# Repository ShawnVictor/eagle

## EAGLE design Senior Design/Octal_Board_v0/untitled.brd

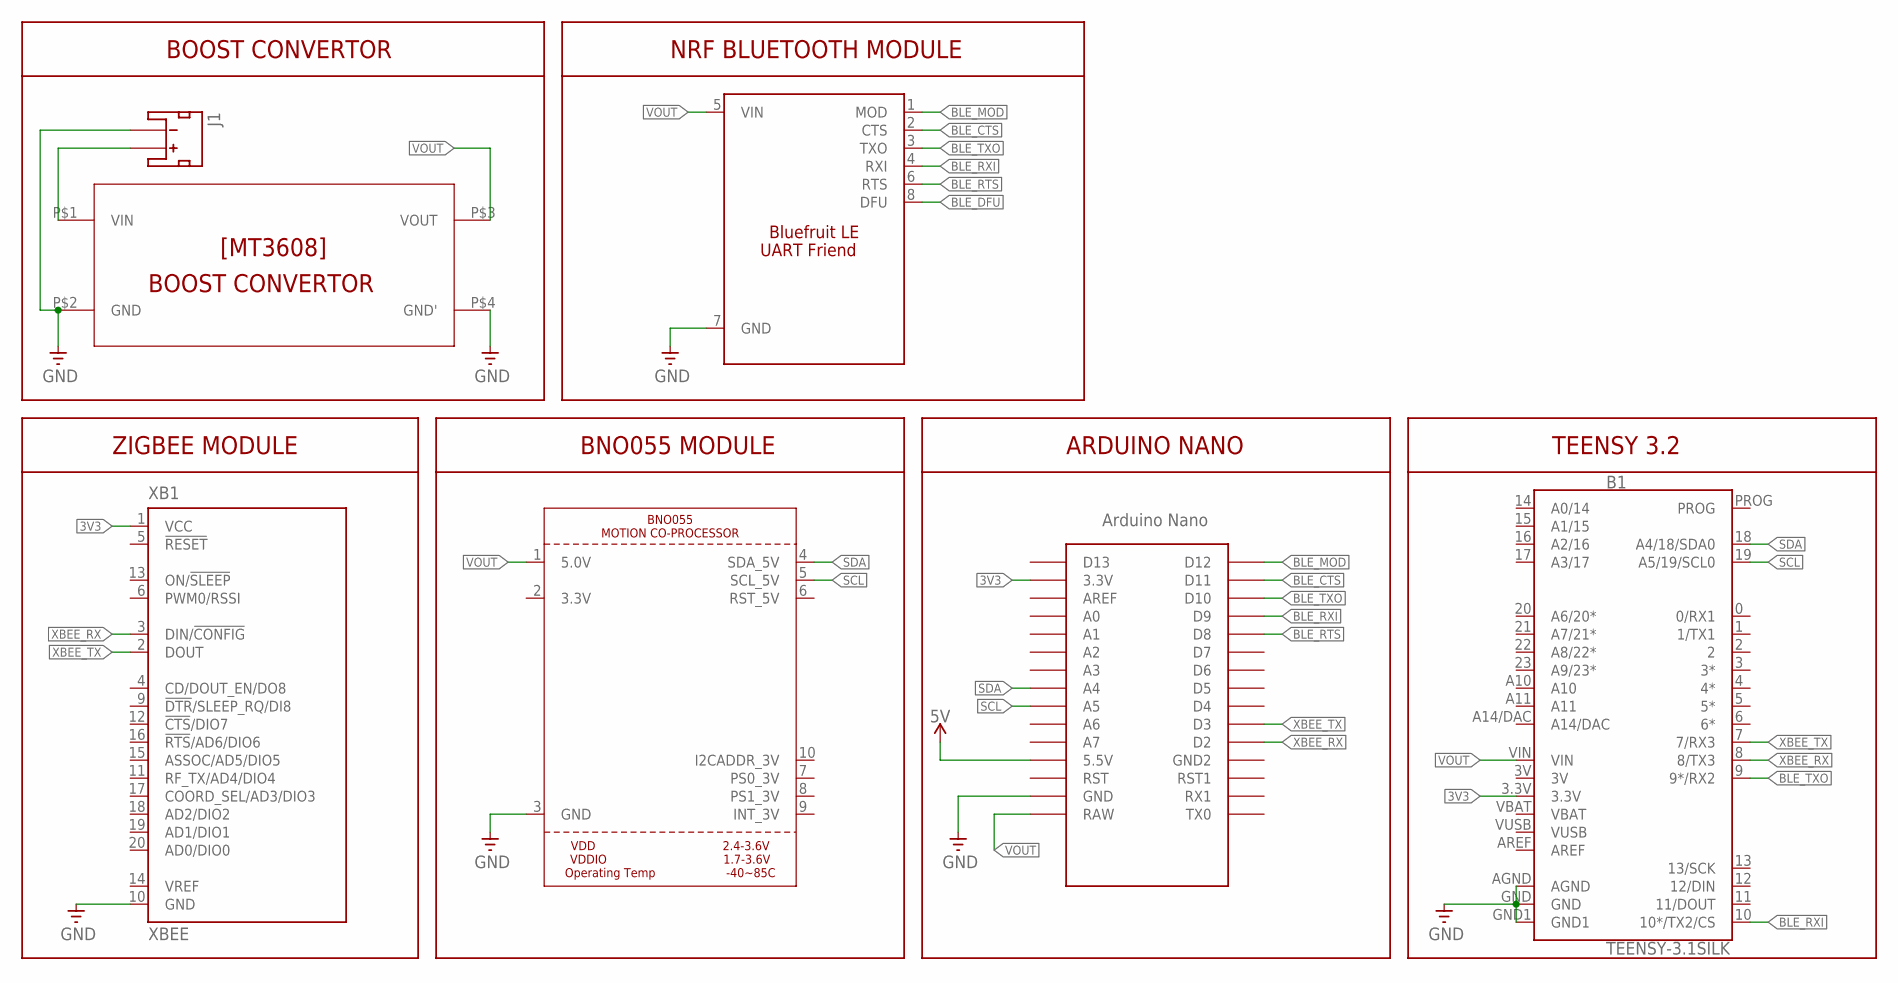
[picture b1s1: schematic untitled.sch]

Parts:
B1: TEENSY-3.1SILK; TEENSY-3.1
J1: JST_2MM_MALE; JST-2-SMD
U$1: NANO
U$2: BNO055; BNO
U$3: MT3608
U$4: BLUEFRUIT_LE; BLUETOOTH_FRIEND
XB1: XBEE

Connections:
3V: B1.3V
3V3: B1.3.3V, U$1.3.3V, XB1.1 (VCC)
5V: U$1.5V (5.5V)
BLE_CTS: U$1.D11, U$4.2 (CTS)
BLE_DFU: U$4.8 (DFU)
BLE_MOD: U$1.D12, U$4.1 (MOD)
BLE_RTS: U$1.D8, U$4.6 (RTS)
BLE_RXI: B1.10 (10*/TX2/CS), U$1.D9, U$4.4 (RXI)
BLE_TXO: B1.9 (9*/RX2), U$1.D10, U$4.3 (TXO)
GND: B1.AGND, B1.GND, B1.GND1, J1.1 (-), U$1.GND, U$2.3 (GND), U$3.P$2 (GND), U$3.P$4 (GND'), U$4.7 (GND), XB1.10 (GND)
unnamed: J1.2 (+), U$3.P$1 (VIN)
SCL: B1.19 (A5/19/SCL0), U$1.A5, U$2.5 (SCL_5V)
SDA: B1.18 (A4/18/SDA0), U$1.A4, U$2.4 (SDA_5V)
VBAT: B1.VBAT
VOUT: B1.VIN, U$1.RAW, U$2.1 (5.0V), U$3.P$3 (VOUT), U$4.5 (VIN)
VUSB: B1.VUSB
XBEE_RX: B1.8 (8/TX3), U$1.D2, XB1.3 (DIN/!CONFIG)
XBEE_TX: B1.7 (7/RX3), U$1.D3, XB1.2 (DOUT)

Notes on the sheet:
ZIGBEE MODULE
BNO055 MODULE
ARDUINO NANO
TEENSY 3.2
BOOST CONVERTOR
NRF BLUETOOTH MODULE

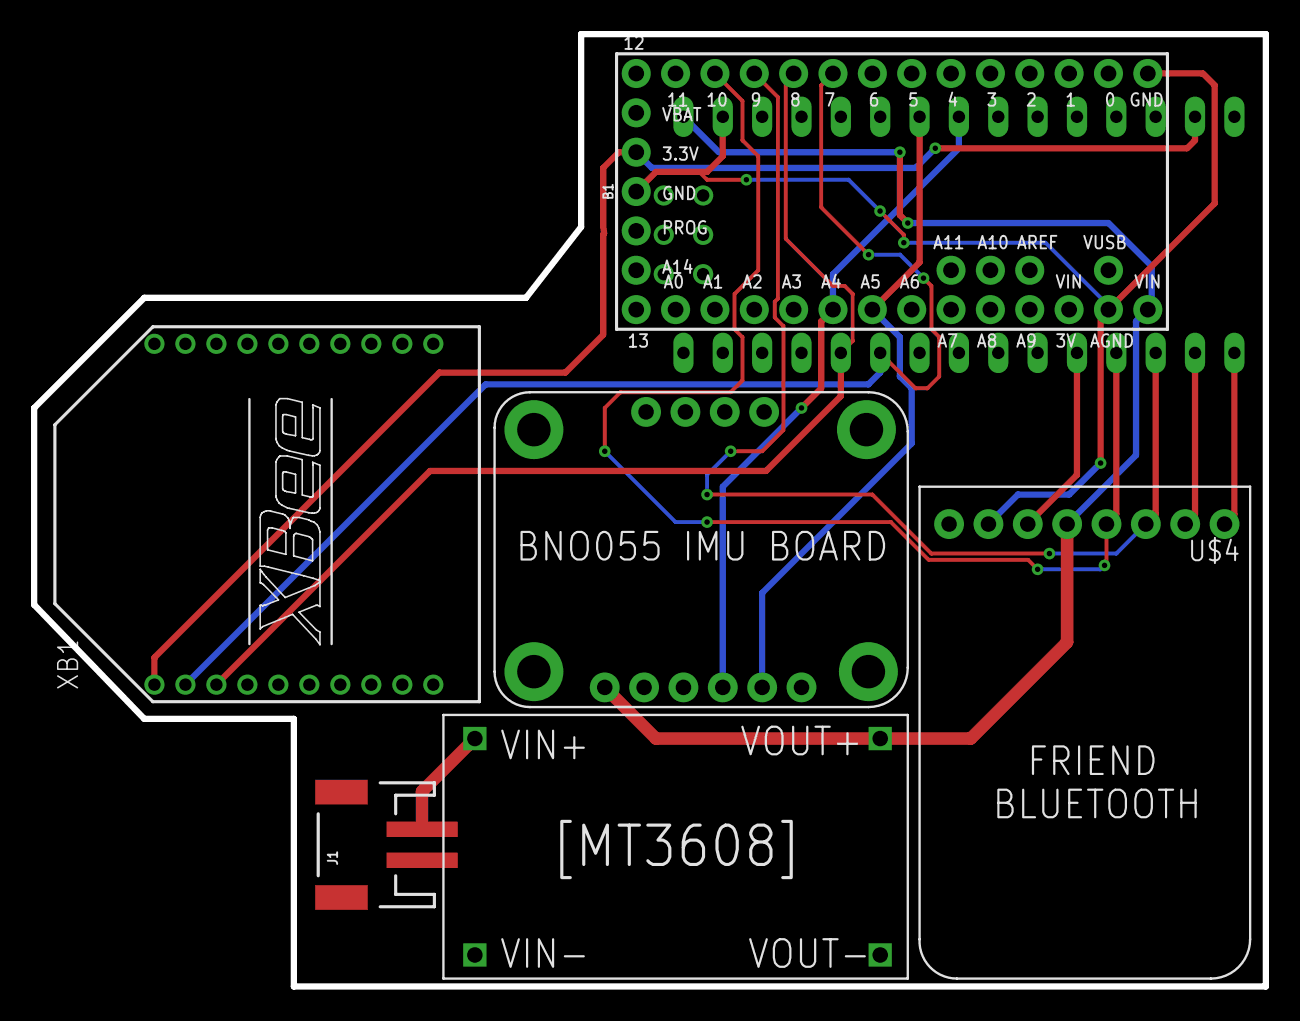
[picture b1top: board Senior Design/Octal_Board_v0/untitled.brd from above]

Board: 2 copper layers, 79.5 x 61.5 mm, 7 parts (0 on the bottom side), 13 nets.

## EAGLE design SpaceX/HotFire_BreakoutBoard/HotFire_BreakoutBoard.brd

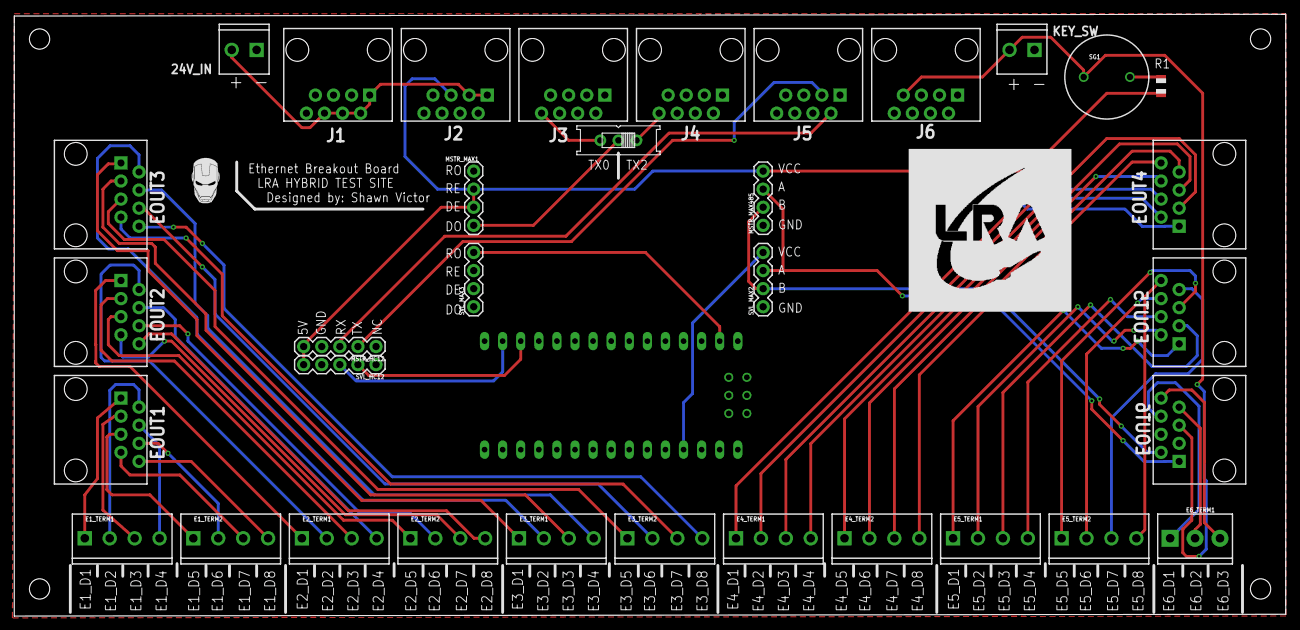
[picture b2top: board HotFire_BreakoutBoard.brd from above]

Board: 2 copper layers, 178.5 x 84.5 mm, 35 parts (0 on the bottom side), 59 nets.

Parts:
24V_IN: SCREWTERMINAL-3.5MM-2
E1_TERM1, E1_TERM2, E2_TERM1, E2_TERM2, E3_TERM1, E3_TERM2, E4_TERM1, E4_TERM2, E5_TERM1, E5_TERM2: SCREWTERMINAL-3.5MM-4
E6_TERM1: SCREWTERMINAL-3.5MM-3
EOUT1, EOUT2, EOUT3, EOUT4, EOUT5, EOUT6: RJ45; RJ45-8
J1, J2, J3, J4, J5, J6: RJ45; RJ45-8
KEY_SW: SCREWTERMINAL-3.5MM-2
MSTR_HC12: 1X05
MSTR_MAX1, MSTR_MAX485: 1X04
R1: 100; R0805
S1: EG1218
SG1: BUZZERPTH; BUZZER-12MM
SVL_HC12: 1X05
SVL_MAX2, SVL_MAX3: 1X04
U$4: NANO

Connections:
5.0V: J2.5, MSTR_HC12.5, MSTR_MAX1.2, MSTR_MAX1.3, MSTR_MAX485.4, R1.2, SVL_HC12.5
+24V: 24V_IN.2, J1.1, J1.2, J1.4, J1.6, J2.1, J2.3
D1/TX0: J3.8, S1.S
D10: SVL_HC12.2, U$4.D10
D11: SVL_HC12.3, U$4.D11
E1_D1: E1_TERM1.1, EOUT1.1
E1_D2: E1_TERM1.2, EOUT1.2
E1_D3: E1_TERM1.3, EOUT1.3
E1_D4: E1_TERM1.4, EOUT1.4
E1_D5: E1_TERM2.1, EOUT1.5
E1_D6: E1_TERM2.2, EOUT1.6
E1_D7: E1_TERM2.3, EOUT1.7
E1_D8: E1_TERM2.4, EOUT1.8
E2_D1: E2_TERM1.1, EOUT2.1
E2_D2: E2_TERM1.2, EOUT2.2
E2_D3: E2_TERM1.3, EOUT2.3
E2_D4: E2_TERM1.4, EOUT2.4
E2_D5: E2_TERM2.1, EOUT2.5
E2_D6: E2_TERM2.2, EOUT2.6
E2_D7: E2_TERM2.3, EOUT2.7
E2_D8: E2_TERM2.4, EOUT2.8
E3_D1: E3_TERM1.1, EOUT3.1
E3_D2: E3_TERM1.2, EOUT3.2
E3_D3: E3_TERM1.3, EOUT3.3
E3_D4: E3_TERM1.4, EOUT3.4
E3_D5: E3_TERM2.1, EOUT3.5
E3_D6: E3_TERM2.2, EOUT3.6
E3_D7: E3_TERM2.3, EOUT3.7
E3_D8: E3_TERM2.4, EOUT3.8
E4_D1: E4_TERM1.1, EOUT4.1
E4_D2: E4_TERM1.2, EOUT4.2
E4_D3: E4_TERM1.3, EOUT4.3
E4_D4: E4_TERM1.4, EOUT4.4
E4_D5: E4_TERM2.1, EOUT4.5
E4_D6: E4_TERM2.2, EOUT4.6
E4_D7: E4_TERM2.3, EOUT4.7
E4_D8: E4_TERM2.4, EOUT4.8
E5_D1: E5_TERM1.1, EOUT5.1
E5_D2: E5_TERM1.2, EOUT5.2
E5_D3: E5_TERM1.3, EOUT5.3
E5_D4: E5_TERM1.4, EOUT5.4
E5_D5: E5_TERM2.1, EOUT5.5
E5_D6: E5_TERM2.2, EOUT5.6
E5_D7: E5_TERM2.3, EOUT5.7
E5_D8: E5_TERM2.4, EOUT5.8
E6_D1: E6_TERM1.1, EOUT6.6
E6_D2: E6_TERM1.2, EOUT6.7
E6_D3: E6_TERM1.3, EOUT6.8
ETHERNET8: J4.8, S1.O
ETHERNET10: J5.2, MSTR_HC12.3
ETHERNET11: J5.3, MSTR_HC12.2
GND: 24V_IN.1, EOUT6.3, EOUT6.4, J1.8, J6.8, KEY_SW.1, MSTR_HC12.4, MSTR_MAX485.1, SVL_HC12.4, SVL_MAX2.1, SVL_MAX3.2, SVL_MAX3.3, U$4.GND
KEY_SW+: EOUT6.5, J6.7, KEY_SW.2, SG1.-
MAX_A: EOUT6.1, MSTR_MAX485.3, SVL_MAX2.3
MAX_B: EOUT6.2, MSTR_MAX485.2, SVL_MAX2.2
unnamed: MSTR_MAX1.1, S1.P
unnamed: R1.1, SG1.+
SLV_RX: SVL_MAX3.4, U$4.RX1
SVL_5V: SVL_MAX2.4, U$4.5V

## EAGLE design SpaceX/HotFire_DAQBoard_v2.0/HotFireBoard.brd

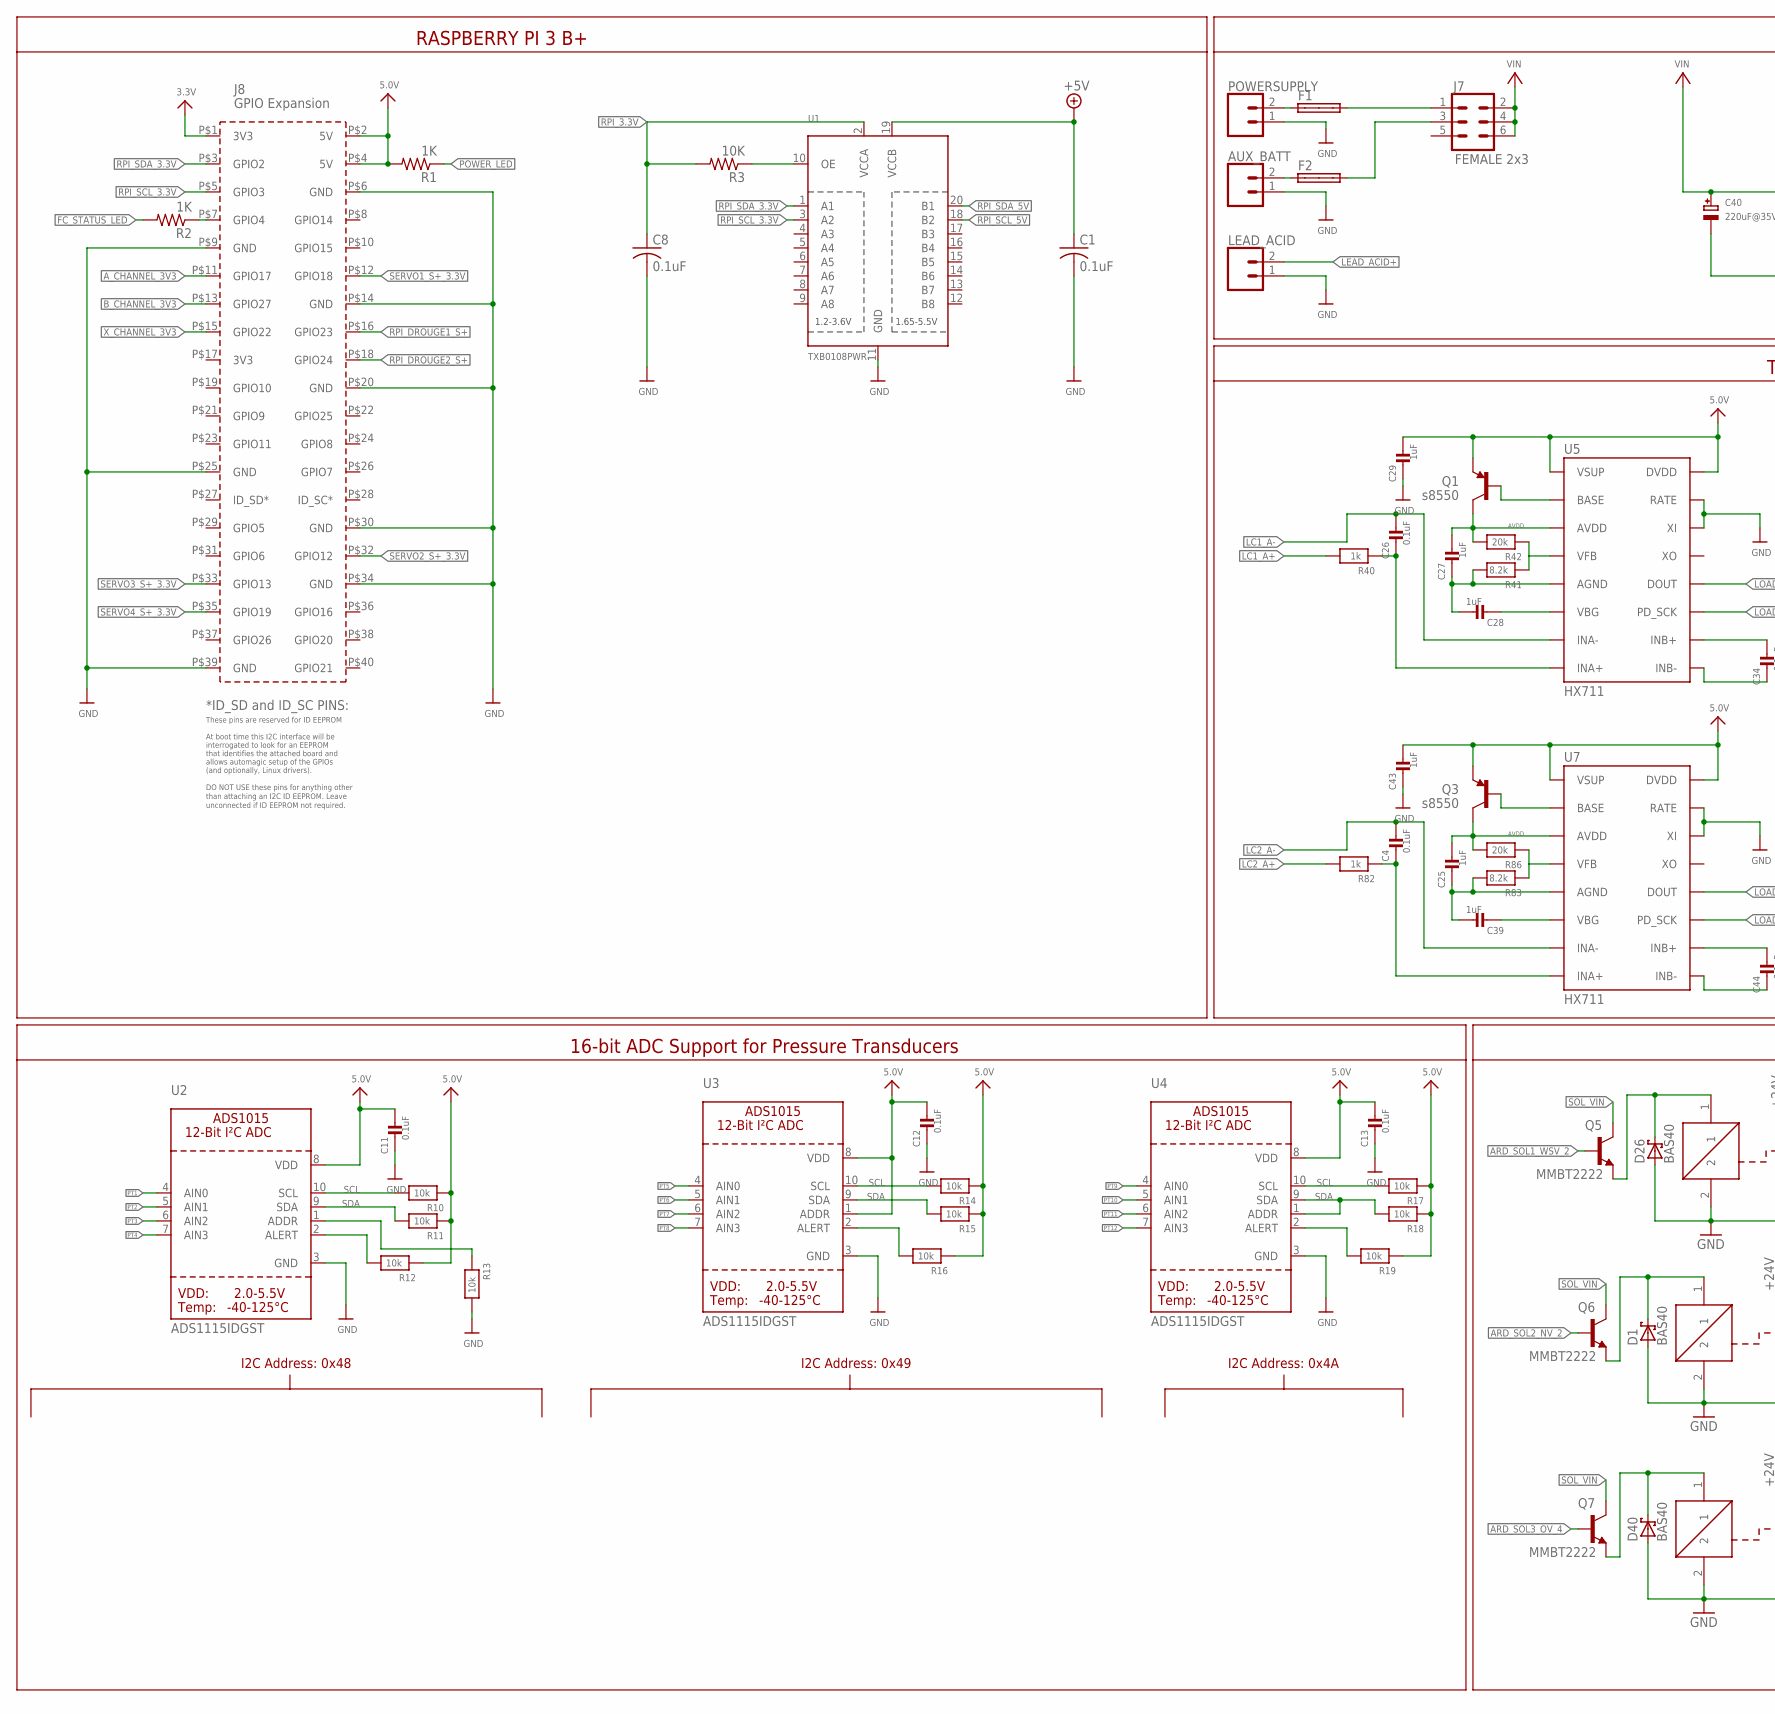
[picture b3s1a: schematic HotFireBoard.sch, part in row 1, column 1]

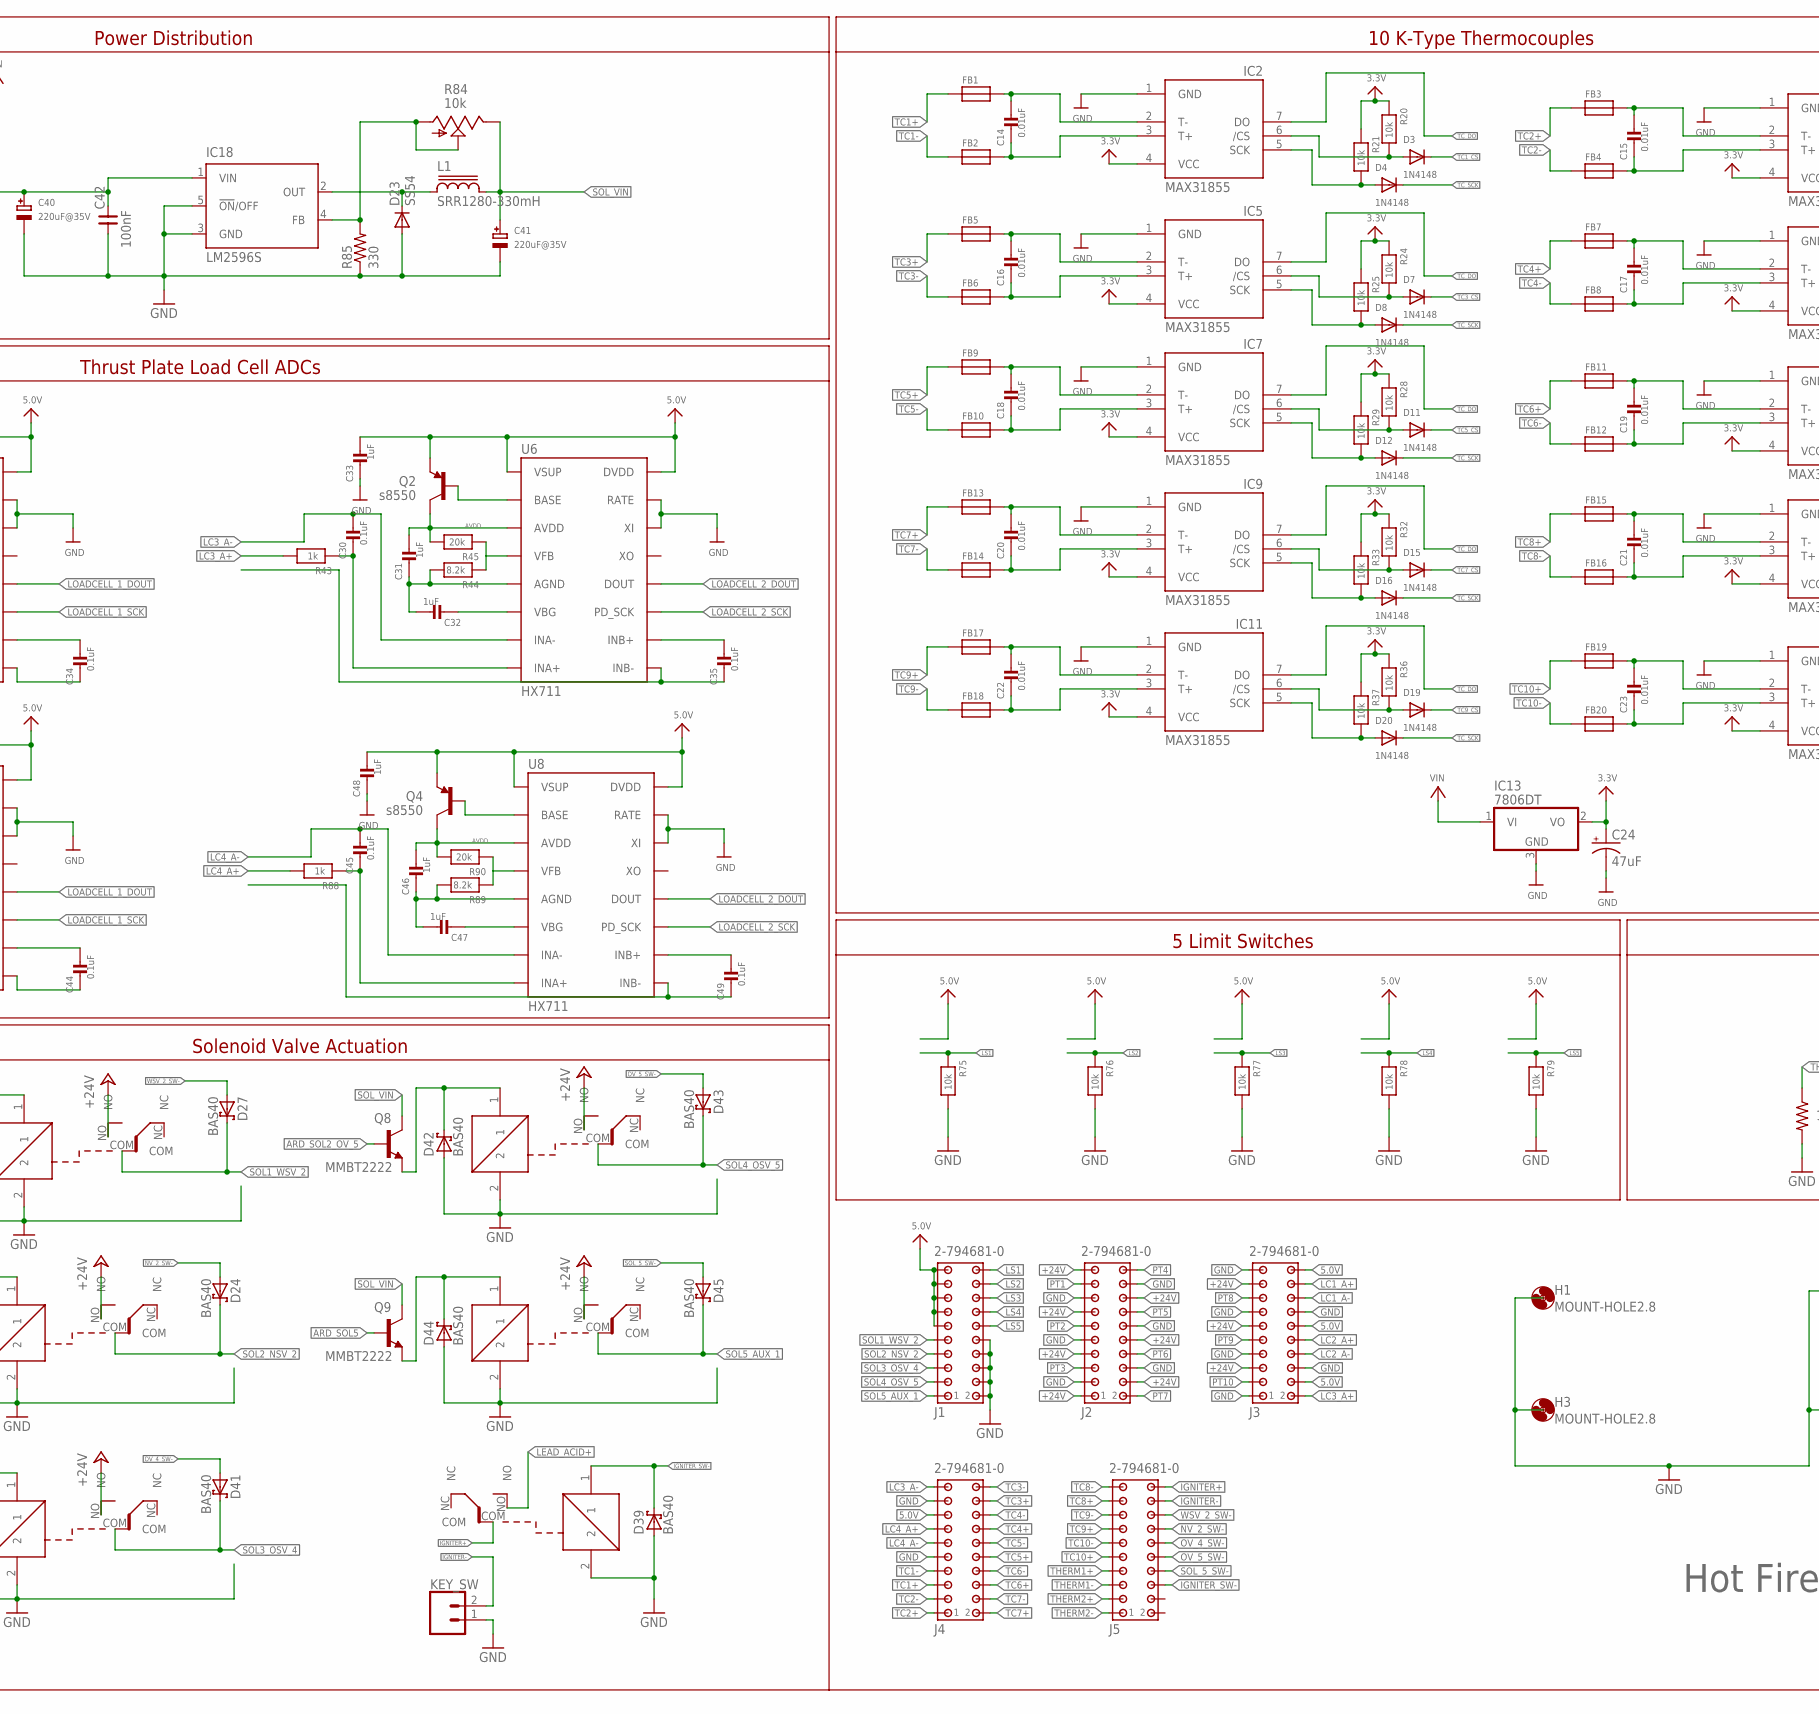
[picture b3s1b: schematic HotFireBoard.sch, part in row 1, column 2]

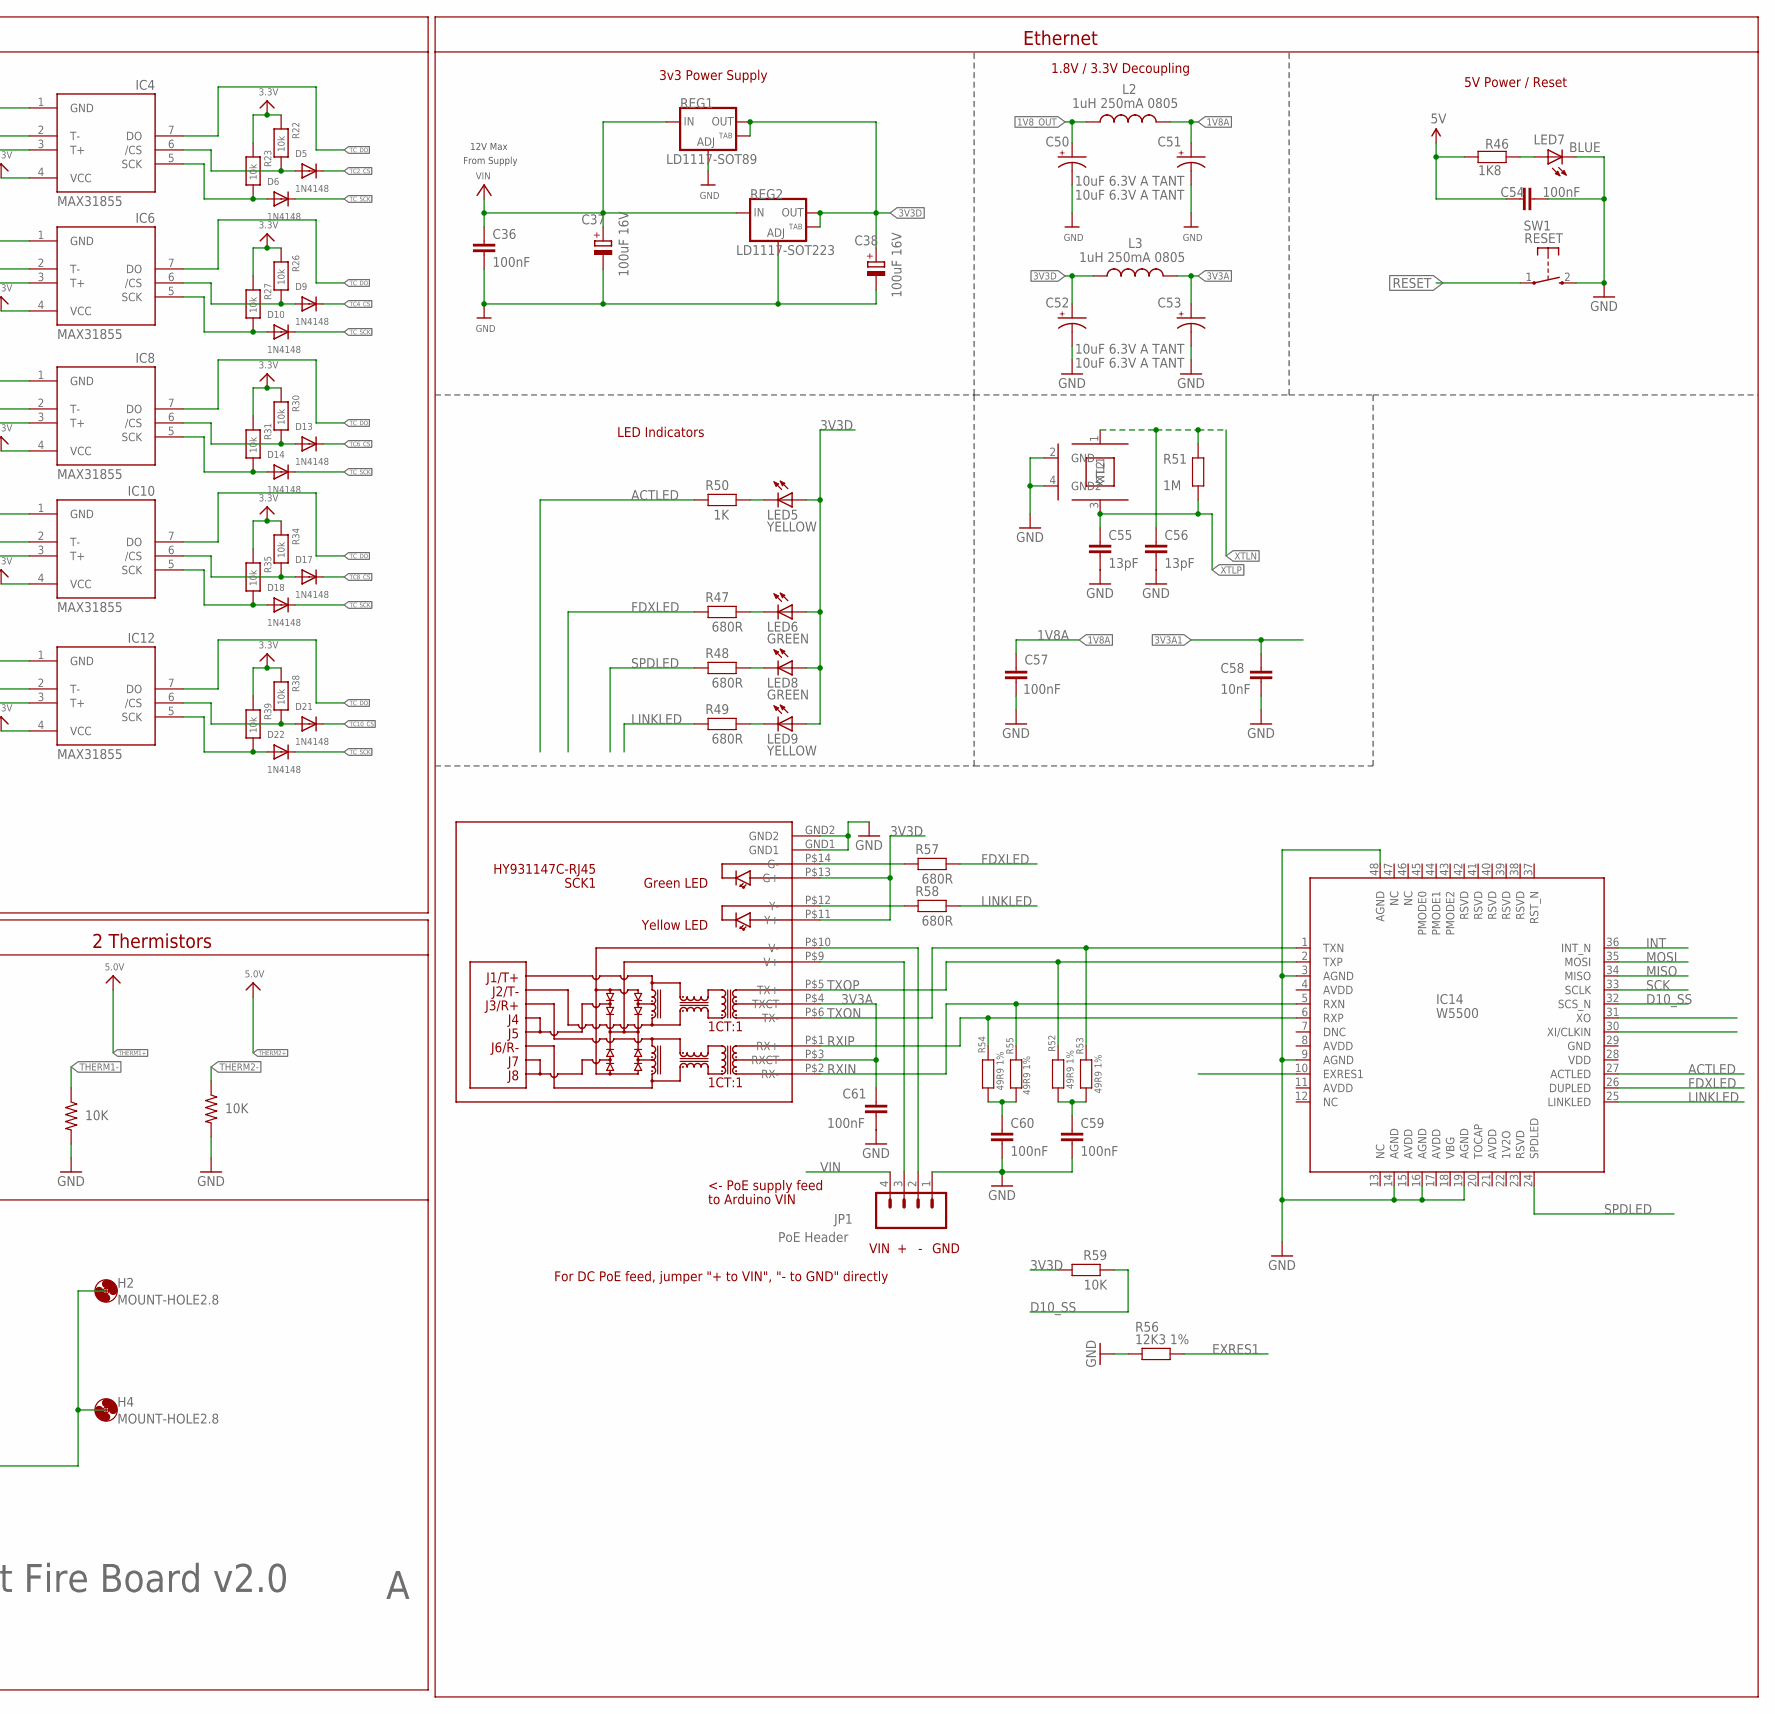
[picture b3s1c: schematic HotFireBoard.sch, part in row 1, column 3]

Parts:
AUX_BATT: CONN_025MM; SCREWTERMINAL-5MM-2
C1, C8: 0.1uF; C0805
C4, C11, C12, C13, C26, C30, C34, C35, C44, C45, C49: 0.1uF; 0805
C14, C15, C16, C17, C18, C19, C20, C21, C22, C23: 0.01uF; 0805
C24: 47uF; PANASONIC_D
C25, C27, C28, C29, C31, C32, C33, C39, C43, C46, C47, C48: 1uF; 0805
C36, C42, C54, C57, C59, C60, C61: 100nF; 0603
C37, C38: 100uF 16V; PANASONIC_D
C40, C41: 220uF@35V; PANASONIC_D
C50, C51, C52, C53: 10uF 6.3V A TANT; EIA3216
C55, C56: 13pF; 0603
C58: 10nF; 0603
D1, D24, D26, D27, D39, D40, D41, D42, D43, D44, D45: BAS40; SOT23
D3, D4, D5, D6, D7, D8, D9, D10, D11, D12, D13, D14, D15, D16, D17, D18, D19, D20, D21, D22: 1N4148; SOD-123
D23: SS54; DO214AB
F1, F2: SHK20L
FB1, FB2, FB3, FB4, FB5, FB6, FB7, FB8, FB9, FB10, FB11, FB12, FB13, FB14, FB15, FB16, FB17, FB18, FB19, FB20: FERRITE; 0603
H1, H2, H3, H4: MOUNT-HOLE2.8; 2,8
IC2, IC4, IC5, IC6, IC7, IC8, IC9, IC10, IC11, IC12: MAX31855; SO08
IC13: 7806DT; TO252
IC14: W5500
IC18: LM2596S; TO263-5
J1, J2, J3, J4, J5: 2-794681-0
J7: FEMALE 2x3; 2X3
JP1: PoE Header; 1X04
KEY_SW: CONN_025MM; SCREWTERMINAL-5MM-2
L1: SRR1280-330mH; SRR1280
L2, L3: 1uH 250mA 0805; L2012C
LEAD_ACID: CONN_025MM; SCREWTERMINAL-5MM-2
LED5, LED9: YELLOW; LED-0603
LED6, LED8: GREEN; LED-0603
LED7: BLUE; LED-0603
PCB1: RPI3
POWERSUPPLY: CONN_025MM; SCREWTERMINAL-5MM-2
Q1, Q2, Q3, Q4: s8550; TO-92
Q5, Q6, Q7, Q8, Q9: MMBT2222; SOT223
R1, R2: 1K; R0603
R3: 10K; R0805
R10, R11, R12, R13, R14, R15, R16, R17, R18, R19, R20, R21, R22, R23, R24, R25, R26, R27, R28, R29, R30, R31, R32, R33, R34, R35, R36, R37, R38, R39, R75, R76, R77, R78, R79: 10k; 0805
R40, R43, R82, R88: 1k; 0805
R41, R44, R83, R89: 8.2k; 0805
R42, R45, R86, R90: 20k; 0805
R46: 1K8; 0603
R47, R48, R49, R57, R58: 680R; 0603
R50: 1K; 0603
R51: 1M; 0603
R52, R53, R54, R55: 49R9 1%; 0603
R56: 12K3 1%; 0603
R59: 10K; 0603
R80, R81: 10K; M0805
R84: 10k; S64W
R85: 330; R0603
REG1: LD1117-SOT89; SOT89
REG2: LD1117-SOT223; SOT223
SCK1: HY931147C-RJ45; HY931147C
SW1: RESET; TACTILE_SWITCH_SMD_2PIN_TINY
U1: TXB0108PWR; TSSOP20
U2, U3, U4: ADS1115IDGST; MSOP10
U5, U6, U7, U8: HX711; SO16
U$15, U$17, U$19, U$21, U$128, U$138: RW-SH
XTL1: 25MHZ; CRYSTAL-SMD-3X2

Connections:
1V8A: C51.A (+), C57.1, L2.2
1V8_OUT: C50.A (+), L2.1
3V3A: C53.A (+), C61.1, L3.2, SCK1.P$3 (RXCT), SCK1.P$4 (TXCT)
3V3A1: C58.1
3V3D: C38.+, C52.A (+), L3.1, LED5.A, LED6.A, LED8.A, LED9.A, R59.2, REG1.2 (OUT), REG1.4 (OUT), REG2.2 (OUT), REG2.4 (OUT), SCK1.P$11 (Y+), SCK1.P$13 (G+)
5V: C54.1, R46.1
+24V: J2.1, J2.4, J2.7, J2.10, J2.13, J2.16, J2.19, J3.5, J3.11, J3.17, U$15.NO, U$17.NO, U$19.NO, U$21.NO, U$128.NO
ACTLED: IC14.27 (ACTLED), R50.2
ARD_SOL1_WSV_2: Q5.1 (B); also elsewhere on the board
ARD_SOL2_NV_2: Q6.1 (B); also elsewhere on the board
ARD_SOL2_OV_5: Q8.1 (B)
ARD_SOL3_OV_4: Q7.1 (B); also elsewhere on the board
ARD_SOL5: Q9.1 (B); also elsewhere on the board
AVDD: C25.2, C27.2, C31.2, C46.2, Q1.3 (C), Q2.3 (C), Q3.3 (C), Q4.3 (C), R42.2, R45.2, R86.2, R90.2, U5.3 (AVDD), U6.3 (AVDD), U7.3 (AVDD), U8.3 (AVDD)
D0/RX0: PCB1.P$3 (GPIO2), U1.1 (A1); also elsewhere on the board
D1/TX0: U1.5 (A4); also elsewhere on the board
D10_SS: IC14.32 (SCS_N), R59.1
D+: U1.15 (B5); also elsewhere on the board
D-: U1.16 (B4); also elsewhere on the board
EXRES1: IC14.10 (EXRES1), R56.2
FDXLED: IC14.26 (DUPLED), R47.2, R57.1
IGNITER+: J5.20, U$138.COM
IGNITER-: J5.18, KEY_SW.2
IGNITER_SW-: D39.3 (C), J5.6, U$138.1
INT: IC14.36 (INT_N)
LC1_A+: J3.18, R40.2
LC1_A-: C26.2, J3.16, U5.7 (INA-)
LC2_A+: J3.10, R82.2
LC2_A-: C4.2, J3.8, U7.7 (INA-)
LC3_A+: J3.2, R43.2
LC3_A-: C30.2, J4.19, U6.7 (INA-)
LC4_A+: J4.13, R88.2
LC4_A-: C45.2, J4.11, U8.7 (INA-)
LEAD_ACID+: LEAD_ACID.2, U$138.NO
LINKLED: IC14.25 (LINKLED), R49.2, R58.1
LOADCELL_1_DOUT: U5.12 (DOUT), U7.12 (DOUT); also elsewhere on the board
LOADCELL_1_SCK: U5.11 (PD_SCK), U7.11 (PD_SCK); also elsewhere on the board
LOADCELL_2_DOUT: U6.12 (DOUT), U8.12 (DOUT); also elsewhere on the board
LOADCELL_2_SCK: U6.11 (PD_SCK), U8.11 (PD_SCK); also elsewhere on the board
LS1: J1.20, R75.1; also elsewhere on the board
LS2: J1.18, R76.1; also elsewhere on the board
LS3: J1.16, R77.1; also elsewhere on the board
LS4: J1.14, R78.1; also elsewhere on the board
LS5: J1.12, R79.1; also elsewhere on the board
MISO: IC14.34 (MISO); also elsewhere on the board
MOSI: IC14.35 (MOSI); also elsewhere on the board
unnamed: F1.1A, POWERSUPPLY.2
unnamed: AUX_BATT.2, F2.1A
unnamed: F1.2A, J7.1
unnamed 103: U1.22; also elsewhere on the board
unnamed 104: U1.23; also elsewhere on the board
unnamed: C14.1, FB2.2, IC2.3 (T+)
unnamed: PCB1.P$5 (GPIO3), U1.3 (A2)
unnamed: C14.2, FB1.2, IC2.2 (T-)
unnamed: F2.2A, J7.3
unnamed: D3.A, IC2.6 (/CS), R20.2
unnamed: C59.1, R52.1, R53.2
unnamed: C4.1, R82.1, U7.8 (INA+)
unnamed: D23.C, IC18.2 (OUT), L1.1
unnamed: R12.2, U2.2 (ALERT)
unnamed: IC18.4 (FB), R84.A, R84.S, R85.2
unnamed: R16.2, U3.2 (ALERT)
unnamed: R13.1, U2.1 (ADDR)
unnamed: R57.2, SCK1.P$14 (G-)
unnamed: JP1.3, SCK1.P$9 (V+)
unnamed: R19.2, U4.2 (ALERT)
unnamed: C25.1, C39.2, R83.2, U7.5 (AGND)
unnamed: JP1.2, SCK1.P$10 (V-)
unnamed: D4.A, IC2.5 (SCK), R21.2
unnamed: C15.2, FB3.2, IC4.2 (T-)
unnamed: C39.1, U7.6 (VBG)
unnamed: R83.1, R86.1, U7.4 (VFB)
unnamed: C15.1, FB4.2, IC4.3 (T+)
unnamed: D5.A, IC4.6 (/CS), R22.2
unnamed: D6.A, IC4.5 (SCK), R23.2
unnamed: C16.2, FB5.2, IC5.2 (T-)
unnamed: C16.1, FB6.2, IC5.3 (T+)
unnamed: D7.A, IC5.6 (/CS), R24.2
unnamed: D8.A, IC5.5 (SCK), R25.2
unnamed: C17.2, FB7.2, IC6.2 (T-)
unnamed: C17.1, FB8.2, IC6.3 (T+)
unnamed: D9.A, IC6.6 (/CS), R26.2
unnamed: D10.A, IC6.5 (SCK), R27.2
unnamed: C18.2, FB9.2, IC7.2 (T-)
unnamed: C18.1, FB10.2, IC7.3 (T+)
unnamed: D11.A, IC7.6 (/CS), R28.2
unnamed: D12.A, IC7.5 (SCK), R29.2
unnamed: C19.2, FB11.2, IC8.2 (T-)
unnamed: C19.1, FB12.2, IC8.3 (T+)
unnamed: D13.A, IC8.6 (/CS), R30.2
unnamed: D14.A, IC8.5 (SCK), R31.2
unnamed: C20.2, FB13.2, IC9.2 (T-)
unnamed: C20.1, FB14.2, IC9.3 (T+)
unnamed: D15.A, IC9.6 (/CS), R32.2
unnamed: D16.A, IC9.5 (SCK), R33.2
unnamed: C21.2, FB15.2, IC10.2 (T-)
unnamed: C21.1, FB16.2, IC10.3 (T+)
unnamed: D17.A, IC10.6 (/CS), R34.2
unnamed: D18.A, IC10.5 (SCK), R35.2
unnamed: C22.2, FB17.2, IC11.2 (T-)
unnamed: C22.1, FB18.2, IC11.3 (T+)
unnamed: D19.A, IC11.6 (/CS), R36.2
unnamed: D20.A, IC11.5 (SCK), R37.2
unnamed: C23.2, FB19.2, IC12.2 (T-)
unnamed: C23.1, FB20.2, IC12.3 (T+)
unnamed: D21.A, IC12.6 (/CS), R38.2
unnamed: D22.A, IC12.5 (SCK), R39.2
unnamed: C26.1, R40.1, U5.8 (INA+)
unnamed: C27.1, C28.2, R41.2, U5.5 (AGND)
unnamed: C28.1, U5.6 (VBG)
unnamed: R41.1, R42.1, U5.4 (VFB)
unnamed: Q1.2 (B), U5.2 (BASE)
unnamed: C30.1, R43.1, U6.8 (INA+)
unnamed: C31.1, C32.2, R44.2, U6.5 (AGND)
unnamed: C32.1, U6.6 (VBG)
unnamed: R44.1, R45.1, U6.4 (VFB)
unnamed: Q2.2 (B), U6.2 (BASE)
unnamed: C34.1, U5.9 (INB-)
unnamed: C34.2, U5.10 (INB+)
unnamed: C35.1, U6.9 (INB-)
unnamed: C35.2, U6.10 (INB+)
unnamed: D26.3 (C), Q5.3 (E), U$128.1
unnamed: D1.3 (C), Q6.3 (E), U$15.1
unnamed: D40.3 (C), Q7.3 (E), U$17.1
unnamed: D42.3 (C), Q8.3 (E), U$19.1
unnamed: LED7.A, R46.2
unnamed: D44.3 (C), Q9.3 (E), U$21.1
unnamed: Q3.2 (B), U7.2 (BASE)
unnamed: C44.1, U7.9 (INB-)
unnamed: C44.2, U7.10 (INB+)
unnamed: C45.1, R88.1, U8.8 (INA+)
unnamed: C46.1, C47.2, R89.2, U8.5 (AGND)
unnamed: C47.1, U8.6 (VBG)
unnamed: R89.1, R90.1, U8.4 (VFB)
unnamed: Q4.2 (B), U8.2 (BASE)
unnamed: C49.1, U8.9 (INB-)
unnamed: C49.2, U8.10 (INB+)
unnamed: C60.1, R54.1, R55.2
unnamed: LED8.C, R48.1
unnamed: LED9.C, R49.1
unnamed: LED6.C, R47.1
unnamed: LED5.C, R50.1
unnamed: R58.2, SCK1.P$12 (Y-)
NV_2_SW-: D24.1 (A), J5.14
OV_4_SW-: D41.1 (A), J5.12
OV_5_SW-: D43.1 (A), J5.10
PT1: J2.17, U2.4 (AIN0)
PT2: J2.11, U2.5 (AIN1)
PT3: J2.5, U2.6 (AIN2)
PT4: J2.20, U2.7 (AIN3)
PT5: J2.14, U3.4 (AIN0)
PT6: J2.8, U3.5 (AIN1)
PT7: J2.2, U3.6 (AIN2)
PT8: J3.15, U3.7 (AIN3)
PT9: J3.9, U4.4 (AIN0)
PT10: J3.3, U4.5 (AIN1)
PT11: U4.6 (AIN2)
PT12: U4.7 (AIN3)
RXIN: IC14.5 (RXN), R55.1, SCK1.P$2 (RX-)
RXIP: IC14.6 (RXP), R54.2, SCK1.P$1 (RX+)
SCK: IC14.33 (SCLK); also elsewhere on the board
SCL: R10.2, R14.2, R17.2, U2.10 (SCL), U3.10 (SCL), U4.10 (SCL); also elsewhere on the board
SDA: R11.2, R15.2, R18.2, U2.9 (SDA), U3.9 (SDA), U4.1 (ADDR), U4.9 (SDA); also elsewhere on the board
SOL1_WSV_2: D27.3 (C), J1.9, U$128.COM
SOL2_NSV_2: D24.3 (C), J1.7, U$15.COM
SOL3_OSV_4: D41.3 (C), J1.5, U$17.COM
SOL4_OSV_5: D43.3 (C), J1.3, U$19.COM
SOL5_AUX_1: D45.3 (C), J1.1, U$21.COM
SOL_5_SW-: D45.1 (A), J5.8
SOL_VIN: C41.+, L1.2, Q5.2 (C), Q6.2 (C), Q7.2 (C), Q8.2 (C), Q9.2 (C), R84.E
SPDLED: IC14.24 (SPDLED), R48.2
TC1+: FB1.1, J4.5
TC1-: FB2.1, J4.7
TC1_CS: D3.C; also elsewhere on the board
TC2+: FB3.1, J4.1
TC2-: FB4.1, J4.3
TC2_CS: D5.C; also elsewhere on the board
TC3+: FB5.1, J4.18
TC3-: FB6.1, J4.20
TC3_CS: D7.C; also elsewhere on the board
TC4+: FB7.1, J4.14
TC4-: FB8.1, J4.16
TC4_CS: D9.C; also elsewhere on the board
TC5+: FB9.1, J4.10
TC5-: FB10.1, J4.12
TC5_CS: D11.C; also elsewhere on the board
TC6+: FB11.1, J4.6
TC6-: FB12.1, J4.8
TC6_CS: D13.C; also elsewhere on the board
TC7+: FB13.1, J4.2
TC7-: FB14.1, J4.4
TC7_CS: D15.C; also elsewhere on the board
TC8+: FB15.1, J5.17
TC8-: FB16.1, J5.19
TC8_CS: D17.C; also elsewhere on the board
TC9+: FB17.1, J5.13
TC9-: FB18.1, J5.15
TC9_CS: D19.C; also elsewhere on the board
TC10+: FB19.1, J5.9
TC10-: FB20.1, J5.11
TC10_CS: D21.C; also elsewhere on the board
TC_DO: IC2.7 (DO), IC4.7 (DO), IC5.7 (DO), IC6.7 (DO), IC7.7 (DO), IC8.7 (DO), IC9.7 (DO), IC10.7 (DO), IC11.7 (DO), IC12.7 (DO); also elsewhere on the board
TC_SCK: D4.C, D6.C, D8.C, D10.C, D12.C, D14.C, D16.C, D18.C, D20.C, D22.C; also elsewhere on the board
THERM1+: J5.7
THERM1-: J5.5, R80.1
THERM2+: J5.3
THERM2-: J5.1, R81.1
TXON: IC14.1 (TXN), R53.1, SCK1.P$6 (TX-)
TXOP: IC14.2 (TXP), R52.2, SCK1.P$5 (TX+)
VIN: C36.1, C37.+, C40.+, C42.2, IC13.1 (VI), IC18.1 (VIN), J7.2, J7.4, J7.6, JP1.4, REG1.3 (IN), REG2.3 (IN); also elsewhere on the board
WSV_2_SW-: D27.1 (A), J5.16
XTAL1: PCB1.P$7 (GPIO4), R2.1; also elsewhere on the board
XTLN: C56.1, R51.2, XTL1.1 (XTL1)
XTLP: C55.1, R51.1, XTL1.3 (XTL2)

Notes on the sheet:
I2C Address: 0x48
I2C Address: 0x49
I2C Address: 0x4A
RASPBERRY PI 3 B+
Power Distribution
Thrust Plate Load Cell ADCs
16-bit ADC Support for Pressure Transducers
Solenoid Valve Actuation
10 K-Type Thermocouples
5 Limit Switches
2 Thermistors
Hot Fire Board v2.0
Ethernet
12V Max
From Supply
3v3 Power Supply
1.8V / 3.3V Decoupling
5V Power / Reset
LED Indicators
VIN
GND
<- PoE supply feed
For DC PoE feed, jumper "+ to VIN", "- to GND" directly
to Arduino VIN

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

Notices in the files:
parts and their libraries:
SparkFun-Boards: Licensing: Creative Commons ShareAlike 4.0 International - https://creativecommons.org/licenses/by-sa/4.0
inductor-bourns: Copyright (C) 2008, Bob Starr
dframes: Copyright (C) 2004, Bob Starr (bobstarr@mindspring.com)
